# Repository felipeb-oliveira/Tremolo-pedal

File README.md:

# Tremolo pedal

## About
A Tremolo effect pedal, which modulates the guitar signal's amplitude by a generated triangular wave with adjustable frequency. The modulation frequency range is from about 0.5Hz to 10Hz. The circuit has the following stages:

1. Input: guitar signal reception by a P10 (6.35mm) Jack;
2. Oscillator: using a NE555, a square symmetrycal wave is generated, and converted to a triangular wave (with the frequency adjustable by a potentiometer). The wave then passes through a Op Amp buffer;
3. Amplification: The guitar signal is amplified by a ratio of about 2.5 with no distortion/clipping. This is needed because there is power loss at the modulation stage;
4. Modulation: After the amplification, the guitar signal goes through a variable resistor (representing the 'Depth' of the effect) in series with a LDR (Light Dependent Resistor), illuminated by a Led supplied by the oscillator (see the schematic, might get confusing). When the generated wave (from -2V to +2V) is > 0, the LED lights up and the LDR reduces its resistance greatly (from about 2M to about 50k on the best scenario), and the output is the tension divided by these 2 resistors. Since the LDR resistance never reaches zero, there is power loss. Hence, the amplification stage is required. It's basically a voltage divider, with the grounded resistance being the LDR (varying from 2M to 50k), and the 'supply' resistance being the Depth level.
5. Output: modulated signal goes to a P10 Jack.

## Schematic
*These are only the oscillator and modulation circuits, without the inputs, outputs and supply circuits. Please open the Eagle project for the full circuit.*

Oscillator:

Modulation:

## Board

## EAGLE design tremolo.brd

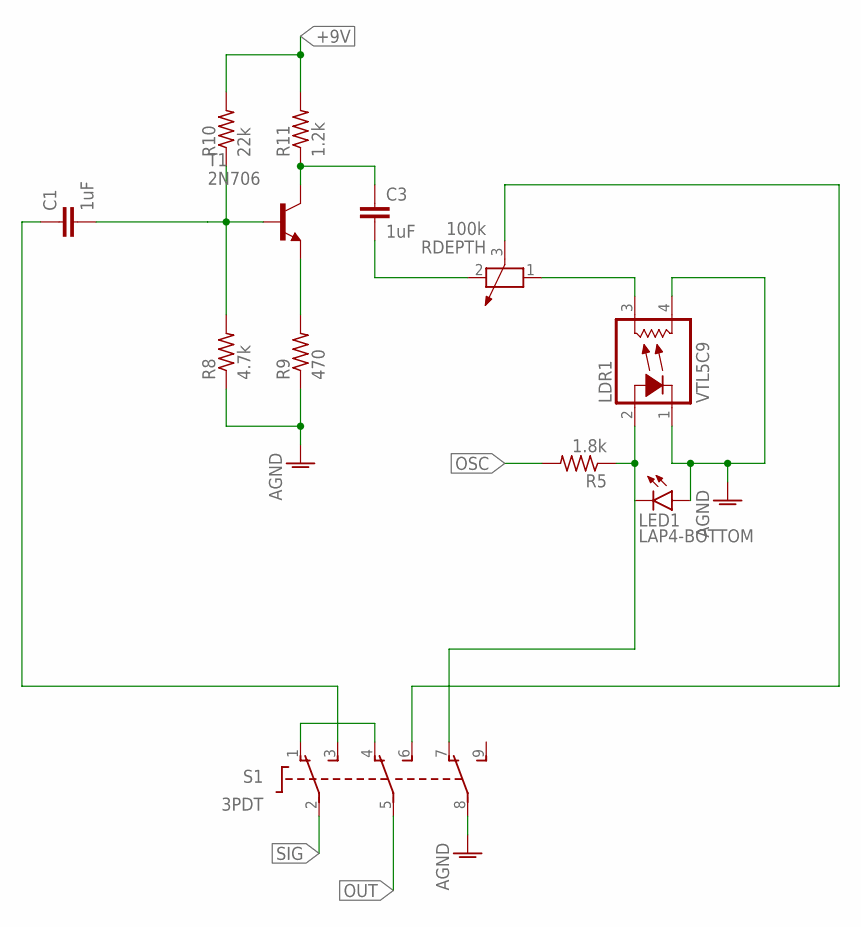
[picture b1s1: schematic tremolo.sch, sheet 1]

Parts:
C1, C3: 1uF; C025-024X044
LDR1: VTL5C9; VTL5C
LED1: LAP4-BOTTOM; P47F-BOTTOM
R5: 1.8k; 0204V
R8: 4.7k; 0204V
R9: 470; 0204V
R10: 22k; 0204V
R11: 1.2k; 0204V
RDEPTH: 100k; PT-10
S1: 3PDT
T1: 2N706; TO18

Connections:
+9V: R10.2, R11.2; also elsewhere on the board
AGND: LDR1.1 (C), LDR1.4 (L2), LED1.A, R8.1, R9.1, S1.8 (P3); also elsewhere on the board
EFX: C3.1, R11.1, RDEPTH.3, S1.6 (S2), T1.3 (C)
IN: C1.1, S1.3 (S1)
unnamed: R9.2, T1.1 (E)
unnamed: C1.2, R8.2, R10.1, T1.2 (B)
unnamed: LDR1.2 (A), LED1.C, R5.1, S1.7 (O3)
unnamed: LDR1.3 (L1), RDEPTH.1
unnamed: S1.1 (O1), S1.4 (O2)
unnamed: C3.2, RDEPTH.2
OSC: R5.2; also elsewhere on the board
OUT: S1.5 (P2); also elsewhere on the board
SIG: S1.2 (P1); also elsewhere on the board

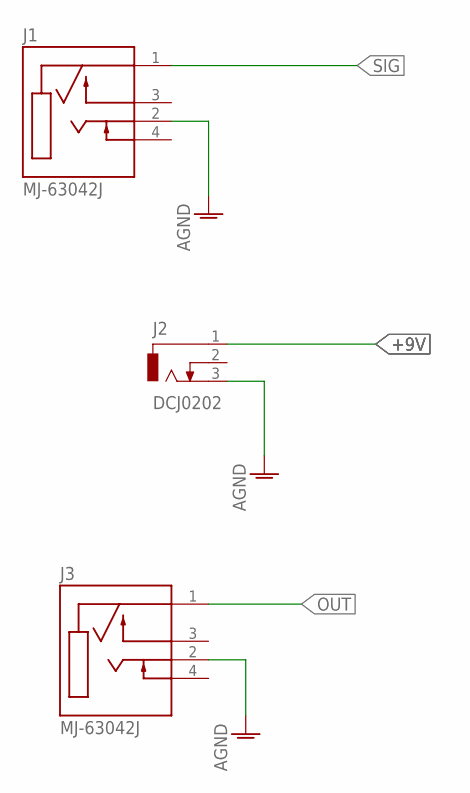
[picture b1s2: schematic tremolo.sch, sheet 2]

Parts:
J1, J3: MJ-63042J; CUI_MJ-63042J
J2: DCJ0202

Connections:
+9V: J2.1; also elsewhere on the board
AGND: J1.2 (TIP), J2.3, J3.2 (TIP); also elsewhere on the board
OUT: J3.1 (SLEEVE); also elsewhere on the board
SIG: J1.1 (SLEEVE); also elsewhere on the board

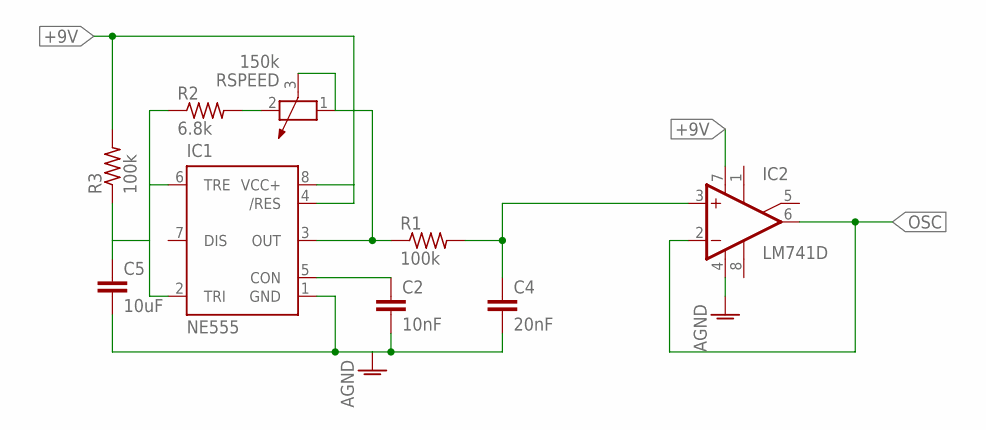
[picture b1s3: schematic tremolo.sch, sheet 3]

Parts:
C2: 10nF; C025-024X044
C4: 20nF; C025-024X044
C5: 10uF; C025-024X044
IC1: NE555; DIL-08
IC2: LM741D; SO08
R1, R3: 100k; 0204V
R2: 6.8k; 0204V
RSPEED: 150k; PT-10

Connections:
+9V: IC1.4 (/RES), IC1.8 (VCC+), IC2.7 (V+), R3.2; also elsewhere on the board
AGND: C2.2, C4.2, C5.2, IC1.1 (GND), IC2.4 (V-); also elsewhere on the board
unnamed: C2.1, IC1.5 (CON)
unnamed: IC1.3 (OUT), R1.1, RSPEED.1, RSPEED.3
unnamed: C5.1, IC1.2 (TRI), IC1.6 (TRE), R2.1, R3.1
unnamed: R2.2, RSPEED.2
OSC: IC2.2 (-IN), IC2.6 (OUT); also elsewhere on the board
WAV: C4.1, IC2.3 (+IN), R1.2

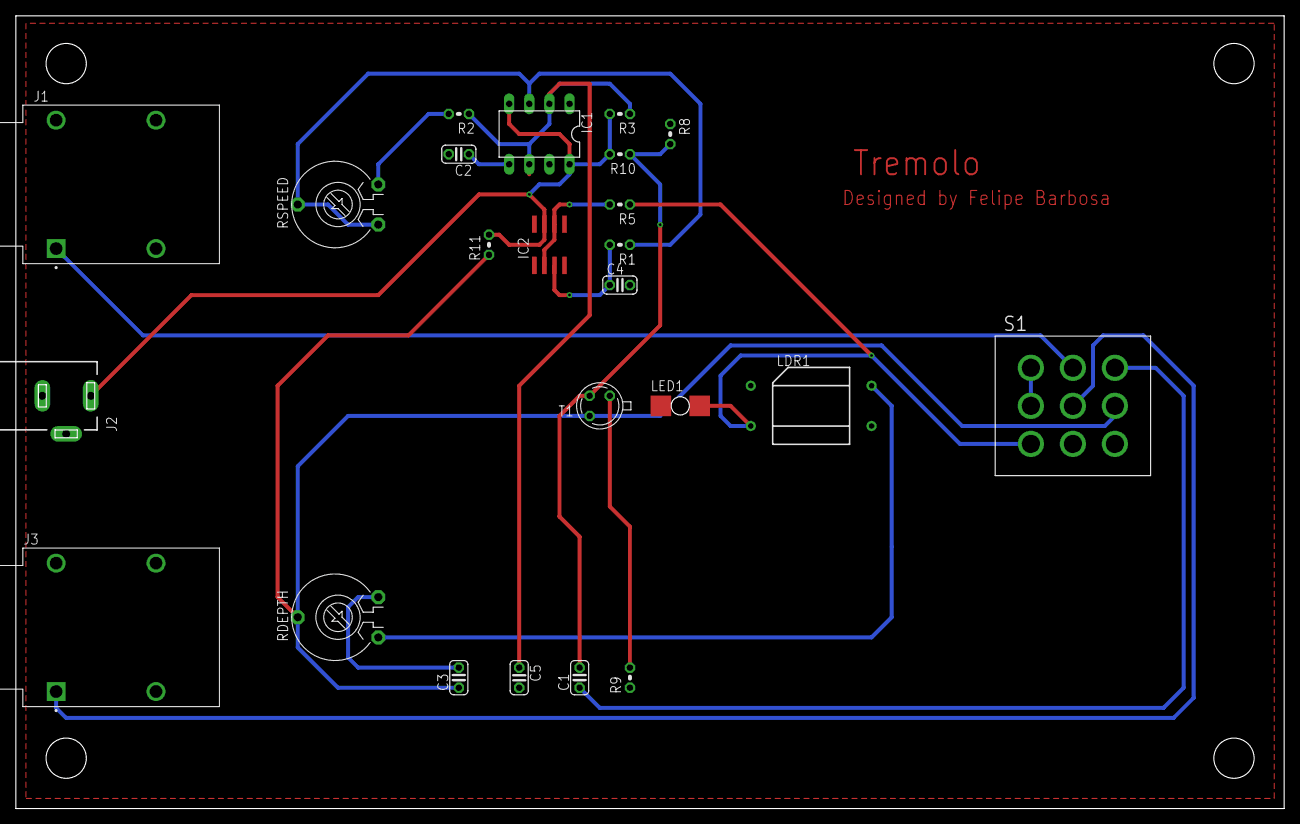
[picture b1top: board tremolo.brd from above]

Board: 2 copper layers, 160.0 x 100.0 mm, 24 parts (0 on the bottom side), 18 nets.
